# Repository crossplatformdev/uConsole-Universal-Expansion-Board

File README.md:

### uConsole Universal Expansion Board

This is a breakout board for the expansion board connector of the ClockworkPi uConsole. You can place small breakout boards into it, and connect them to the uConsole, internally.

| Item            | Link  |
| :---:           | :---: |
| Front           |  |
| Back            |   |
| Schematic       | https://github.com/crossplatformdev/uConsole-Universal-Expansion-Board/blob/main/documents/schematic.pdf |
| Exported files* | https://github.com/crossplatformdev/uConsole-Universal-Expansion-Board/blob/main/export.zip              |

****This is a WIP.*** I need to receive the first batch I ordered to test everything is correct. You can help me verify this files in the meantime. Use with caution.

### Examples of components you can mount on:
This is designed to work with breakout boards, like these:

| Item                               | Image                                         |       
| :---:                              | :---:                                         |
| USB - Anything                     |         |
| USB-A                              |                     |
| USB-B                              |                     |
| USB-C                              |                     |
| RP2040                             |              |
| ESP32                              |                     |
| SD2emmc                            |                 |
| USB2emmc                           |               |
| SD Card                            |                 |
| Arduino modules and breakout boards| |

... And almost everything!

### How to use the board ###
The intended use is to place the components in a way all the pins can be wired, and glue or solder them to the board. 
Then, you can draw traces of tin over the grid, like in this video:

However, I strongly recomend to better use wires. Wires can be bent, and them can cross also; and is less harmful to the board. You can bend and cross the wires like Ben Eater does for his breadboard computer.

| Example          | Video or Picture |
|------------------|------------------|
|Ben Eater's       |    |
|Breadboard        |    |
|Computer          |    |
|Recommmended Way  |   |
|Simplest way      |    |

### Example Recipes ###
- 2xUSB-C, 2xUSB-A (1 internal), USB2emmc (internal), Radxa emmc module.
- 3xUSB-C, 1xUSB-A (1 internal), RTL-SDRv4 (usb dongle, internal)
- RP2040 as board microcontroller + something.
- ESP32 as board microcontroller + something.
- ... expose microcontroller's GPIO through a horizontal pinheader!
- ... or add sensors and modules!
- ... spare data lines can be used as USB!
- You can try to replicate an existing expansion board with breakout boards with this!

(TODO) (First I need to receive the first batch. Star this repo to keep updated)
||

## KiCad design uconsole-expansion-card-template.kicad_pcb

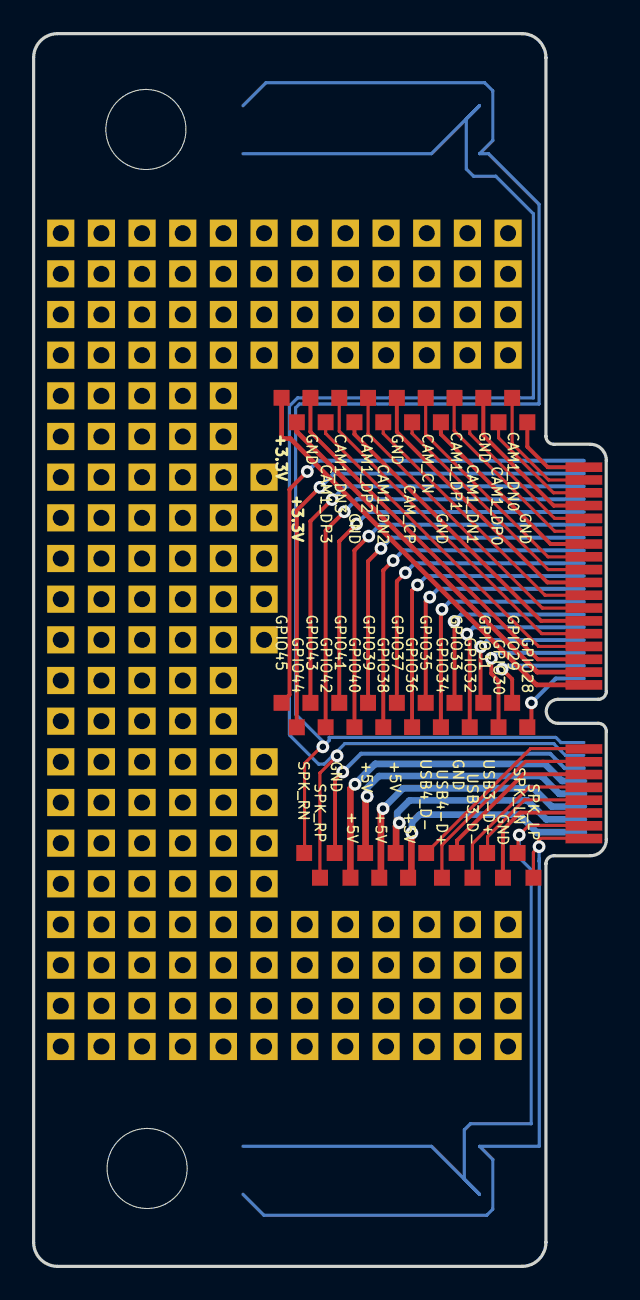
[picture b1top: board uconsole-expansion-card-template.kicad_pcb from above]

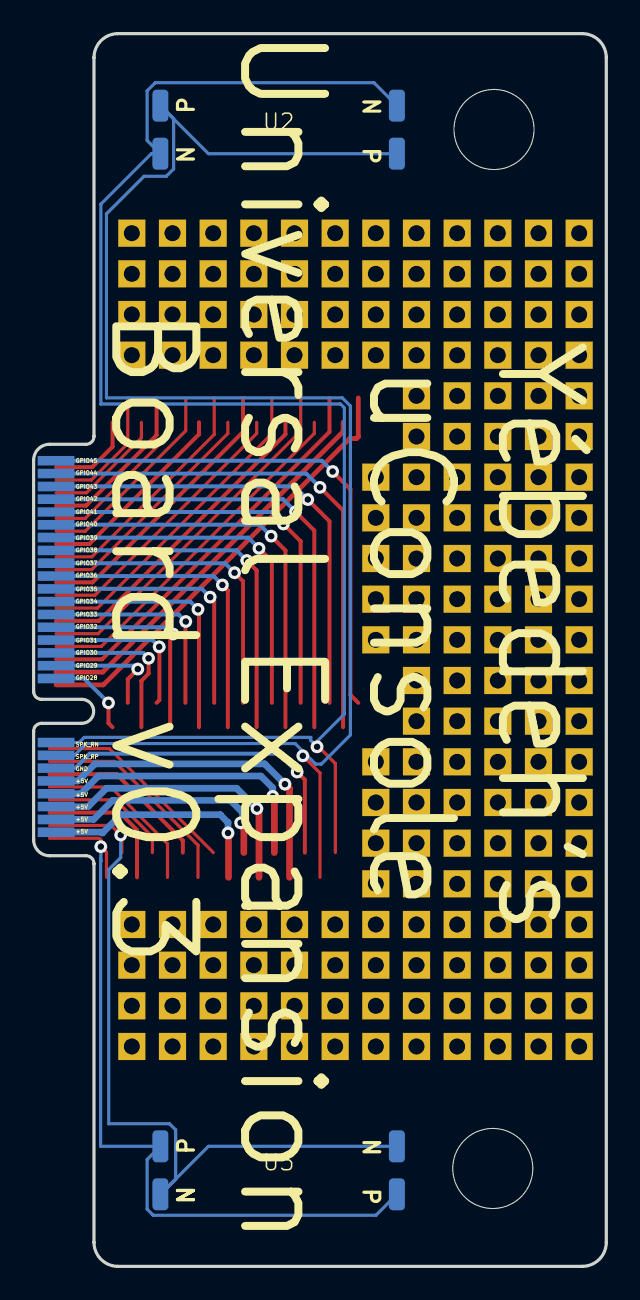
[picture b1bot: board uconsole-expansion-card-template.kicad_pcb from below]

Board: 2 copper layers, 35.8 x 77.0 mm, 206 parts (2 on the bottom side), 33 nets.

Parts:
1, 1#2, 1#3, 1#4, 2, 2#2, 2#3, 2#4, 3, 3#2, 3#3, 3#4, 4, 4#2, 4#3, 4#4, 5, 5#2, 5#3, 5#4, 6, 6#2, 6#3, 6#4, 7, 7#2, 7#3, 7#4, 8, 8#2, 8#3, 8#4, 9, 10, 11, 12, 13, 14, 15, 16, 17, 18, 19, 20, 21, 22, 23, 24, 25, 26, 27, 28, 29, 30, 31, 32, 33, 34, 35, 36, 37, 38, 39, 40, 41, 42, 43, 44, 45, 46, 47, 48, 49, 50, 51, 52, 53, 54, 55, 56, 57, 58, 59, 60, 61, 62, 63, 64, 65, 66, 67, 68, 69, 70, 71, 72, 73, 74, 75, 76, 77, 78, 79, 80, 81, 82, 83, 84, 85, 86, 87, 88, 89, 90, 91, 92, 93, 94, 95, 96, 97, 98, 99, 100, 101, 102, 103, 104, 105, 106, 107, 108, 109, 110, 111, 112, 113, 114, 115, 116, 117, 118, 119, 120, 121, 122, 123, 124, 125, 126, 127, 128, 129, 130, 131, 132, 133, 134, 135, 136, 137, 138, 139, 140, 143, 144, 145, 146, 147, 148, 149, 150, 151, 152, 153, 154, 155, 156, 157, 158, 159, 160, 161, 162, 163, 165, 166, 167, 168, 170, 171, 172, 173, 175, 176, 177, 178, 180, 181, 182, 183: (no value)
H1, H2: MountingHole; MountingHole_5mm
U1: UC EXPANSION; edge-minipcie
U2, U3: Speaker; speaker pads

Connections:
+3V3: U1.17 (3V3), U1.19 (3V3)
+5V: U1.2 (5V), U1.4 (5V), U1.6 (5V), U1.8 (5V), U1.10 (5V)
/CAM1_CN: 5.1, U1.37 (CAM1_CN)
/CAM1_CP: 4#2.1, U1.35 (CAM1_CP)
/CAM1_DN0: 8#3.1, U1.49 (CAM1_DN0)
/CAM1_DN1: 6#4.1, U1.43 (CAM1_DN1)
/CAM1_DN2: 3#4.1, U1.31 (CAM1_DN2)
/CAM1_DN3: 2#4.1, U1.25 (CAM1_DN3)
/CAM1_DP0: 7#2.1, U1.47 (CAM1_DP0)
/CAM1_DP1: 6#2.1, U1.41 (CAM1_DP1)
/CAM1_DP2: 3#2.1, U1.29 (CAM1_DP2)
/CAM1_DP3: 1#2.1, U1.23 (CAM1_DP3)
/GPIO28: 8#2.1, U1.18 (GPIO28)
/GPIO29: 8.1, U1.20 (GPIO29)
/GPIO30: 7#3.1, U1.22 (GPIO30)
/GPIO31: 7.1, U1.24 (GPIO31)
/GPIO32: 6.1, U1.26 (GPIO32)
/GPIO33: 6#3.1, U1.28 (GPIO33)
/GPIO34: 5#3.1, U1.30 (GPIO34)
/GPIO35: 5#4.1, U1.32 (GPIO35)
/GPIO36: 4.1, U1.34 (GPIO36)
/GPIO37: 4#3.1, U1.36 (GPIO37)
/GPIO38: 3.1, U1.38 (GPIO38)
/GPIO39: 3#3.1, U1.40 (GPIO39)
/GPIO40: 2#3.1, U1.42 (GPIO40)
/GPIO41: 2.1, U1.44 (GPIO41)
/GPIO42: 1.1, U1.46 (GPIO42)
/GPIO43: 1#3.1, U1.48 (GPIO43)
/SPEAKER_LN: U1.3 (SPK_LN), U3.2 (N1), U3.4 (N2)
/SPEAKER_LP: U1.1 (SPK_LP), U3.1, U3.3 (P2)
/SPEAKER_RN: U1.16 (SPK_RN), U2.2 (N1), U2.4 (N2)
/SPEAKER_RP: U1.14 (SPK_RP), U2.1, U2.3 (P2)
GND: 1#4.1, 2#2.1, 4#4.1, 5#2.1, 7#4.1, 8#4.1, U1.5 (GND), U1.11 (GND), U1.12 (GND), U1.21 (GND), U1.27 (GND), U1.33 (GND), U1.39 (GND), U1.45 (GND), U1.51 (GND)

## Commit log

2025-01-28 docs
2025-01-28 Components
2025-01-28 Wiring example
2025-01-29 Clearance set to 0.1mm
2025-01-30 Fix misplaced text
2025-01-31 Board 1.27mm passes to production!
2025-02-03 Add wires
2025-02-03 Fix table
2025-03-13 Second Batch
